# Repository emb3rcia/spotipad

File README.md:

# spotipad
Spotify control micropad made for hackpad.hackclub.com
# Background
I have wanted to make something like this for months now. My idea arose when I saw the death of Spotify's "CarThing" which people used as a desk accessory. I didn't have CarThing, so I couldn't use it in this way, so I tried making an improvised one using an old Android phone I had lying around and some live wallpaper app. It didn't work well. Now, when I saw an email in my inbox about hackclub, and saw that I could make a micropad for basically free, I was euphoric. I like to do stuff. I have many ideas for some hardware stuff but don't have funds to bring them to life. Sadly, I discovered hackclub at the end of this "highway." If there will be another "edition," I will do all hands on deck to fully participate. This creation (at least the first iteration) was made in 1 night after 1 too many caffeine capsule (don't do this; it is bad for you 😇). It was also the first time I did PCB and the first time I 3D-designed something that will really be sent to be printed.
# PCB
Please, don't judge me too much, it is my first PCB xD.
## KiCad
- Schematic:

- PCB:

## External Gerber Viewer
- Front

- Back

- Layers

# Case
The case is tilted 40 degrees so you can see the display!.

# Code
Right now, the code is sloppy and probably won't work. The reason is that I don't have the microcontroller yet, so I don't know how to check if the code works, and there's nothing I hate more than writing code blindly without the ability to test it. The current code is more a visualization of my idea:
Spotipad connects normally via USB
Keys and turn-knob send media keys (volume up/down, mute, next/previous track, pause/play).
The screen has 3 options (currently only 1 is “visualized” via demo code).
1. Connect to a locally hosted Flask server that checks the currently played track name and author and sends it via USB Serial Data.
2. Displays text set in config file/GUI (TO:DO)
3. Displays 128x32 image set in config file/GUI (TO:DO)
# Credits
- 3D Models:
1. MX Switch model - [Gal Pavlin](https://grabcad.com/gal.pavlin-2) - [link](https://grabcad.com/library/cherry-mx-switch-2)
2. MX Keycap Model - [Josh Hinnebusch](https://github.com/hineybush/CherryMX/tree/master) - [link](https://github.com/hineybush/CherryMX/tree/master)
3. EC11 Rotary Encoder - [甘草酸不酸](https://grabcad.com/671f3b2e37-1) - [link](https://grabcad.com/library/rotary-encoder-17)
4. SSD1036 0.91" OLED 128x32px display - [John](https://grabcad.com/john-772) - [link](https://grabcad.com/library/0-91in-oled-1)
# BOM
- 1x Seeed XIAO RP2040
- 3x MX-Style switches
- 1x EC11 Rotary encoder
- 1x SSD1036 0.91 inch OLED display
- 3x Blank DSA keycaps
- 4x M3x16mm screws
- 1x 3D printed case (base + top plate)

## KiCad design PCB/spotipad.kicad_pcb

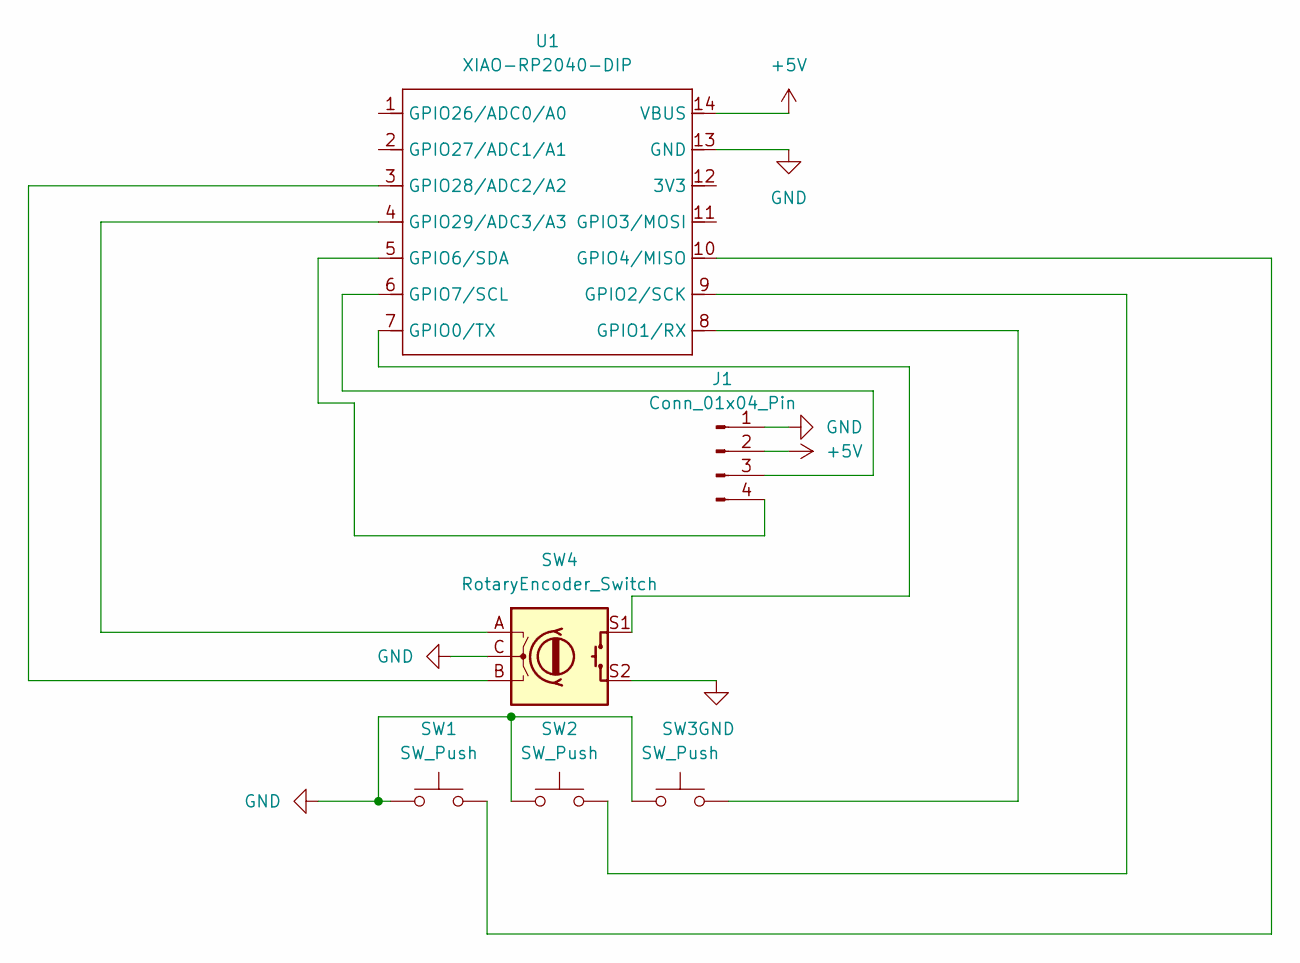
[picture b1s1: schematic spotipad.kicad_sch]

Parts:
J1: Conn_01x04_Pin; SSD1306-0.91-OLED-4pin-128x32
SW1, SW2, SW3: SW_Push; SW_Cherry_MX_1.00u_PCB
SW4: RotaryEncoder_Switch; RotaryEncoder_Alps_EC11E-Switch_Vertical_H20mm
U1: XIAO-RP2040-DIP

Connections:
+5V: J1.2, U1.14 (VBUS)
GND: J1.1, SW1.1, SW2.1, SW3.1, SW4.C, SW4.S2, U1.13 (GND)
unnamed: J1.3, U1.6 (GPIO7/SCL)
unnamed: J1.4, U1.5 (GPIO6/SDA)
unnamed: SW4.S1, U1.7 (GPIO0/TX)
unnamed: SW3.2, U1.8 (GPIO1/RX)
unnamed: SW2.2, U1.9 (GPIO2/SCK)
unnamed: SW1.2, U1.10 (GPIO4/MISO)
unnamed: SW4.B, U1.3 (GPIO28/ADC2/A2)
unnamed: SW4.A, U1.4 (GPIO29/ADC3/A3)

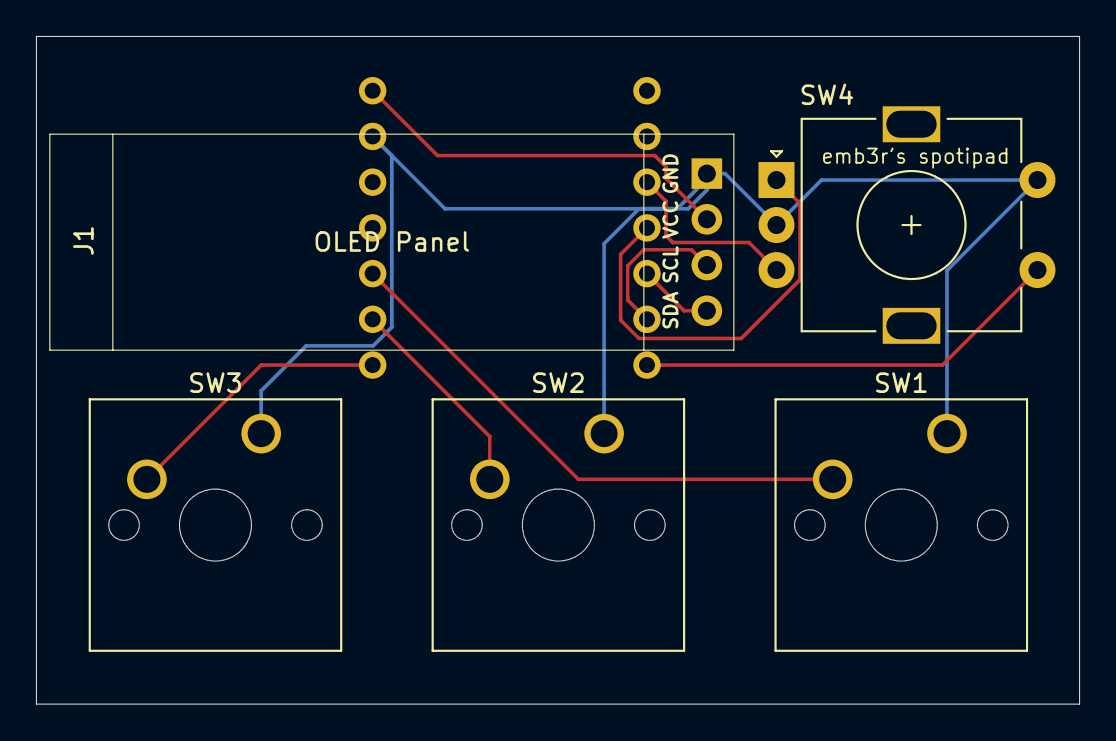
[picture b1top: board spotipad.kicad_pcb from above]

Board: 2 copper layers, 58.0 x 37.1 mm, 6 parts (1 on the bottom side), 10 nets.

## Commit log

2025-07-17 Adding all of the files, making README.md better
